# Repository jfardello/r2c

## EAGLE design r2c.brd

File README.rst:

===
r2c
===

**This is a completely untested trinket "shield".**

The remote remote controller, aka ``r2c`` is lipo charger for the 3v pro trinket
arduino-compatible device, it has a switched battery output that provides 
power management features, an optional infrared diode connected to D3 pin, and an XBEE
socket connected to A7 and A6, (not the HW serial, you can't program the trinket
through the air with this)

.. image:: r2c.png
    :alt: r2c 
    :scale: 50%

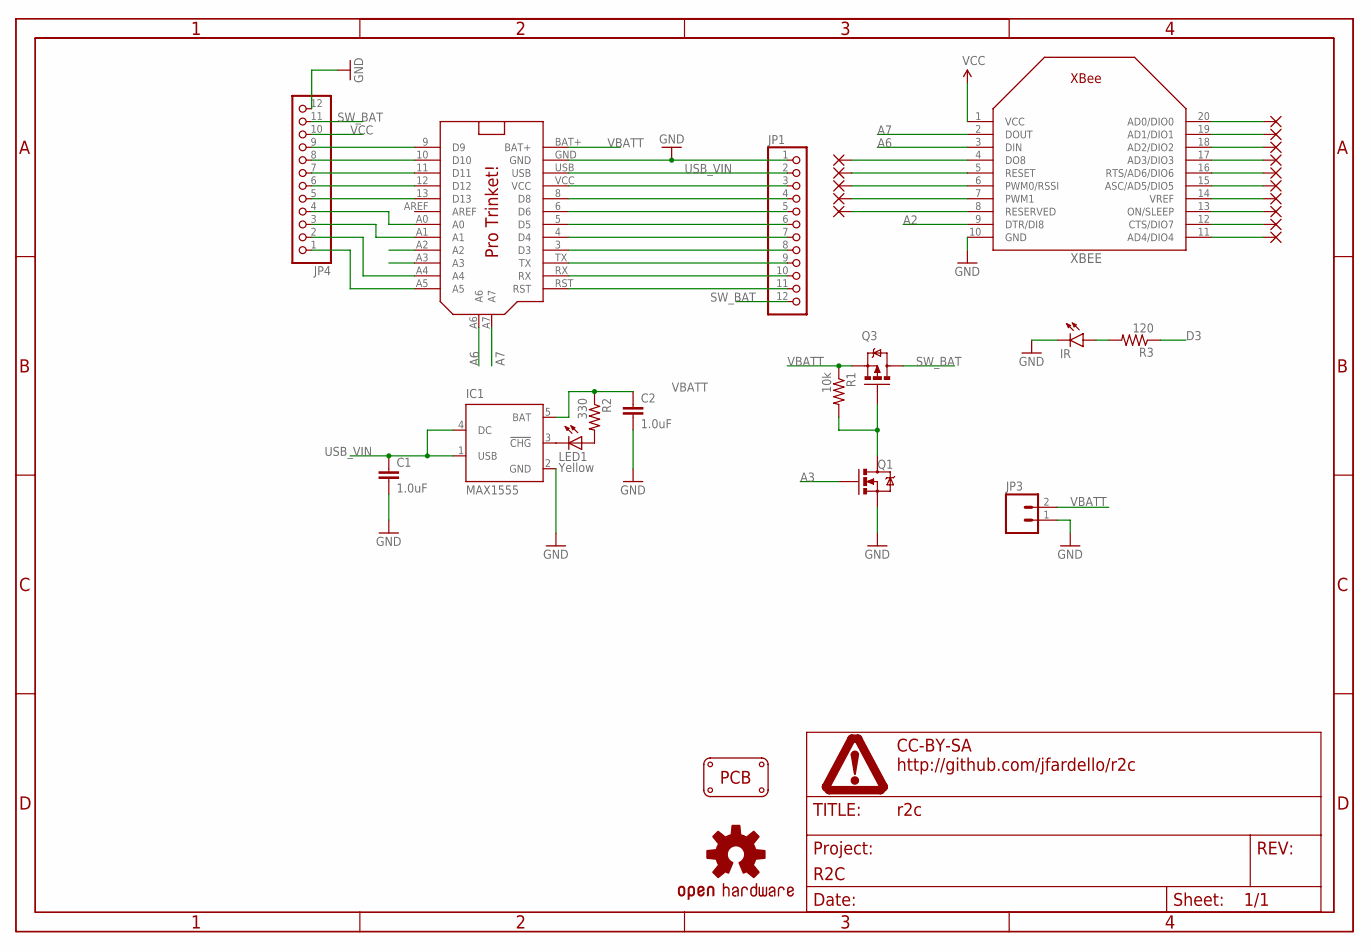
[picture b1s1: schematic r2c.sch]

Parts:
C1, C2: 1.0uF; 0402-CAP
IC1: MAX1555; SOT23-5L
IR: LED3MM
JP1, JP4: PINHD-1X12; 1X12
JP3: M02-JST-2MM-SMT; S2B-PH
LED1: Yellow; LED-0603
LOGO1: OSHW-LOGOS; OSHW-LOGO-S
PAD1, PAD2, PAD3, PAD4, PAD5, PAD6, PAD7, PAD8, PAD9, PAD10, PAD11, PAD12, PAD13, PAD14, PAD15: SMD2; SMD1,27-2,54
PCB1: PCB_DP_RECTANGLE-37X60; DP6037_V1
Q1: MOSFET-NCHANNEL2N7002PW; SOT323
Q3: MOSFET-PCHANNELIRLML2244; SOT23-3
R1: 10k; 0402-RES
R2: 330; 0402-RES
R3: 120; 0402-RES
U$1: PRO_TRINKET; PROTRINKET
U$2: FRAME_DINA4_L; DP_LOGO
XBEE: XBEE

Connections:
A2: U$1.A2, XBEE.9 (DTR/DI8)
A3: Q1.1 (G), U$1.A3
A4: JP4.2, U$1.A4
A5: JP4.1, U$1.A5
A6: U$1.A6, XBEE.3 (DIN)
A7: U$1.A7, XBEE.2 (DOUT)
D3: JP1.8, R3.1, U$1.3 (D3)
GND: C1.2, C2.2, IC1.2 (GND), IR.K (C), JP1.1, JP3.1, JP4.12, Q1.2 (S), U$1.GND, XBEE.10 (GND)
unnamed: Q1.3 (D), Q3.1 (G), R1.2
unnamed: IR.A, R3.2
unnamed: JP1.4, U$1.8 (D8)
unnamed: IC1.3 (!CHG), LED1.C
unnamed: LED1.A, R2.2
unnamed: JP1.5, U$1.6 (D6)
unnamed: PAD1.1, XBEE.20 (AD0/DIO0)
unnamed: JP1.6, U$1.5 (D5)
unnamed: JP1.7, U$1.4 (D4)
unnamed: PAD2.1, XBEE.19 (AD1/DIO1)
unnamed: JP1.9, U$1.TX
unnamed: JP1.10, U$1.RX
unnamed: JP1.11, U$1.RST
unnamed: PAD3.1, XBEE.18 (AD2/DIO2)
unnamed: PAD4.1, XBEE.17 (AD3/DIO3)
unnamed: PAD5.1, XBEE.16 (RTS/AD6/DIO6)
unnamed: PAD6.1, XBEE.15 (ASC/AD5/DIO5)
unnamed: JP4.3, U$1.A1
unnamed: JP4.4, U$1.A0
unnamed: PAD7.1, XBEE.14 (VREF)
unnamed: JP4.5, U$1.13 (D13)
unnamed: JP4.6, U$1.12 (D12)
unnamed: JP4.7, U$1.11 (D11)
unnamed: JP4.8, U$1.10 (D10)
unnamed: JP4.9, U$1.9 (D9)
unnamed: PAD8.1, XBEE.13 (ON/SLEEP)
unnamed: PAD9.1, XBEE.12 (CTS/DIO7)
unnamed: PAD10.1, XBEE.11 (AD4/DIO4)
unnamed: PAD11.1, XBEE.4 (DO8)
unnamed: PAD12.1, XBEE.5 (RESET)
unnamed: PAD13.1, XBEE.6 (PWM0/RSSI)
unnamed: PAD14.1, XBEE.7 (PWM1)
unnamed: PAD15.1, XBEE.8 (RESERVED)
SW_BAT: JP1.12, JP4.11, Q3.3 (D)
USB_VIN: C1.1, IC1.1 (USB), IC1.4 (DC), JP1.2, U$1.USB
VBATT: C2.1, IC1.5 (BAT), JP3.2, Q3.2 (S), R1.1, R2.1, U$1.BAT+
VCC: JP1.3, JP4.10, U$1.VCC, XBEE.1 (VCC)

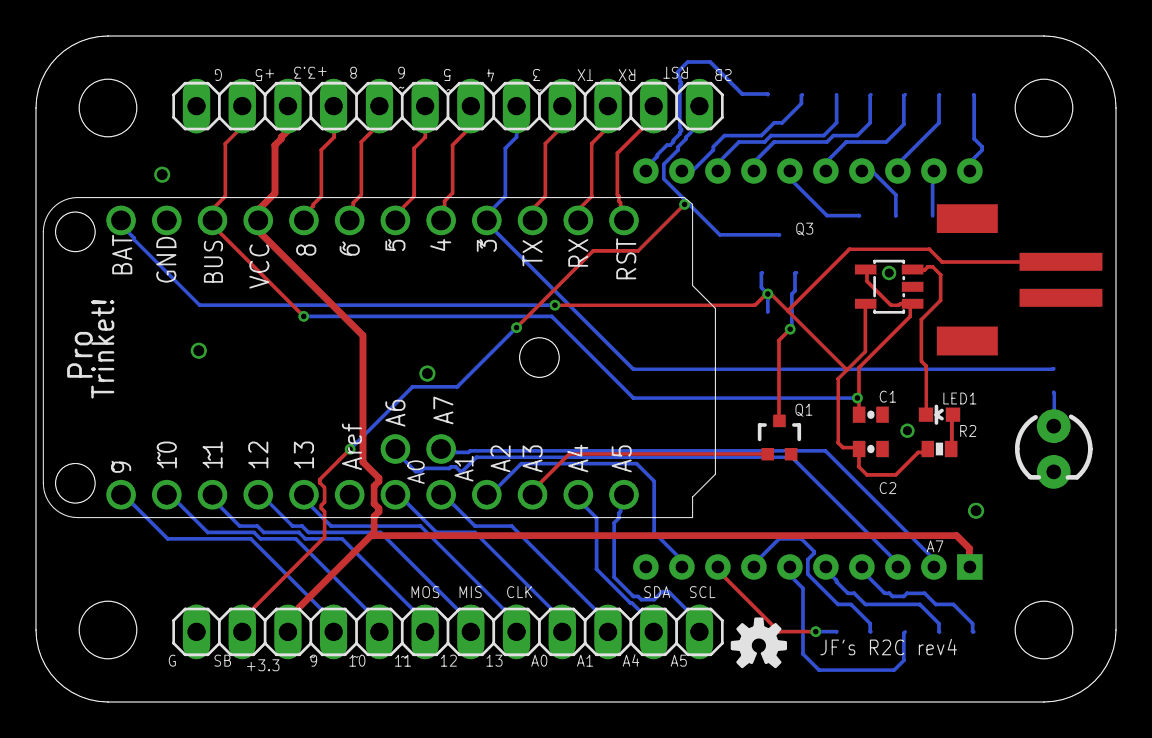
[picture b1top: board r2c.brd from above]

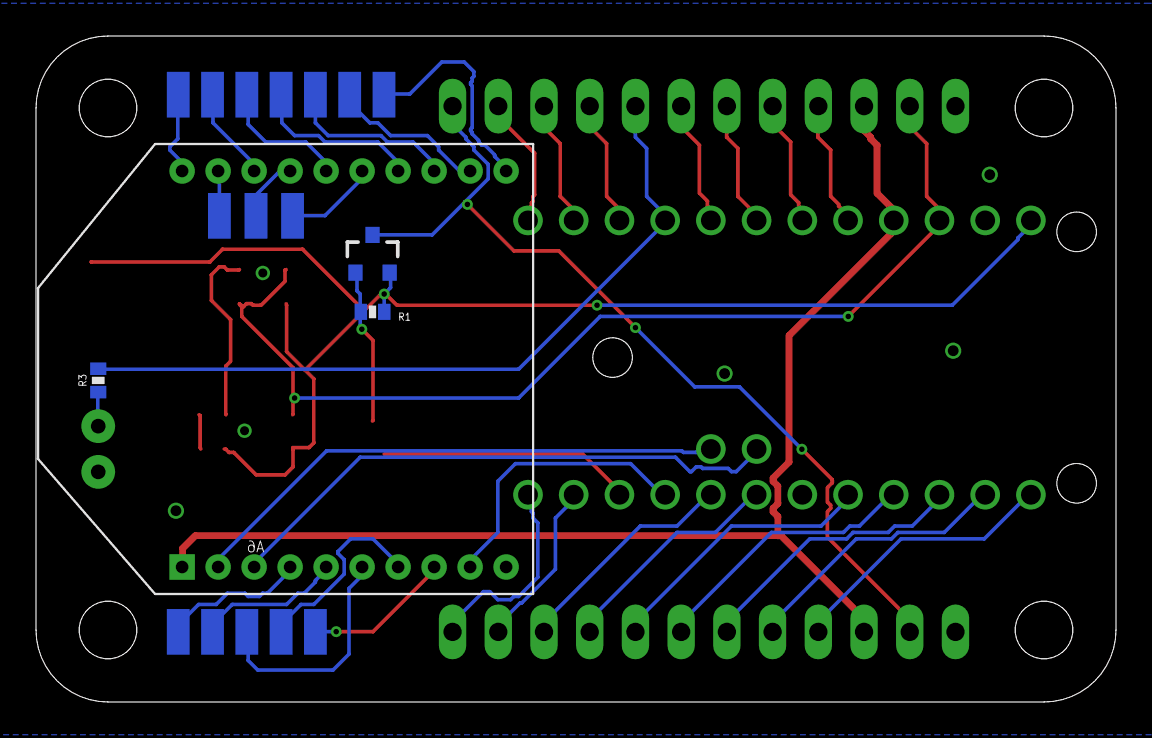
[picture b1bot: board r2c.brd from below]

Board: 2 copper layers, 60.0 x 37.0 mm, 33 parts (19 on the bottom side), 45 nets.

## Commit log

2015-05-24 * Initial commit
2015-05-24 Typo

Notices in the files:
r2c.brd:
LICENSE: CC-BY-SA
parts and their libraries:
SparkFun-DiscreteSemi: Licensing: Creative Commons ShareAlike 4.0 International - https://creativecommons.org/licenses/by-sa/4.0
